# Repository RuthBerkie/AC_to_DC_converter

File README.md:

# AC to DC Converter

This schematic represents a standard linear DC power supply circuit featuring a full-wave bridge rectifier, smoothing filter, and visual power indicator. Its main purpose is to convert alternating current (AC) input into a smooth, stable direct current (DC) output.

1. Component Breakdown & Their Roles

       • J1 (Screw_Terminal_01x02): The AC power input terminal. connecting the external low-voltage AC source, typically coming from a step-down transformer.
       • D1, D3, D4, D5 (1N4007 Diodes): These four diodes form a Full-Wave Bridge Rectifier. Diodes only allow current to flow in one direction. Together, they redirect both the positive and negative halves of the alternating AC wave into a single positive direction, converting AC into pulsating DC.
       • C1 (1000µF Capacitor): The Smoothing/Filter Capacitor. Rectified DC still has massive voltage drops (ripples). C1 stores electrical energy during voltage peaks and releases it during voltage drops, flattening the pulses into a clean, steady DC voltage.
       • R1 (10kΩ Resistor): A Bleeder Resistor. When you turn off or unplug the circuit, C1 can hold a dangerous electrical charge for a long time. R1 provides a safe, continuous path to completely discharge the capacitor when power is disconnected.
       • R2 (2.2kΩ Resistor) & D6 (LED): The Power Indicator. The LED lights up to show that the board is powered and functioning. Because an LED cannot handle raw supply voltage directly, R2 acts as a current-limiting resistor to prevent the LED from burning out.
       • J2 (Screw_Terminal_01x02): The DC power output terminal. This delivers the final, rectified, and smoothed DC voltage to whatever device or external circuit you want to power.
       • H1–H4 (MountingHoles): These are physical holes on the circuit board for screws. They have no electrical function but are used to securely mount the physical PCB into an enclosure.
       • PWR_FLAG & GND: Technical labels used in schematic software (like KiCad). GND establishes the 0V reference line (Ground), while PWR_FLAG informs the software's error-checker that power is properly defined on this net.

The layout follows a logical, left-to-right progression of power processing:
[AC Input: J1] ➔ [Rectification: D1-D5] ➔ [Filtering: C1] ➔ [Bleeding/Indicating: R1, R2+D6] ➔ [DC Output: J2]

    • The AC to Bridge Connections: The two input wires from J1 connect directly to the midpoints of the diode pairs (between D1/D4 and D3/D5). This ensures that regardless of which AC wire is positive at any microsecond, the current is always steered correctly.
    
• Creating the DC Rails:

	• The cathodes (the side with the line symbol) of D1 and D3 join together at the top. This becomes the Positive (+) DC Rail.
	• The anodes of D4 and D5 join together at the bottom. This becomes the Negative (-) DC Rail / Ground.
  
• The Parallel Layout: Components C1, R1, and the R2+D6 branch are connected in parallel across the positive and negative rails.

	• Connecting C1 in parallel allows it to act as a voltage reservoir directly stabilizing the main power lines.
	• Connecting R1 and the LED indicator branch in parallel ensures they continuously experience the full system voltage without blocking current from reaching the final output terminal, J2.

  step-by-step summary of how the entire circuit processes electricity from start to finish:
  
    1. The Input: Alternating Current (AC voltage) enters the circuit through the J1 terminal block on the far left. At this stage, the voltage is constantly fluctuating up and down, reversing its direction multiple times per second.
    2. Rectification: The electricity immediately flows into the Bridge Rectifier (D1, D3, D4, D5). These four diodes act like one-way electrical valves. They redirect the negative halves of the shifting AC wave into the positive direction, transforming it into pulsating Direct Current (DC). 
    3. Smoothing: The pulsating DC moves to the C1 Capacitor. Because the voltage is still pulsing rapidly, the capacitor acts like a temporary water reservoir—it quickly charges up during voltage peaks and discharges energy during the drops. This heavily filters the electrical "ripple," flattening the pulses into a smooth, stable DC voltage.
    4. Safety & Indicator: On its way to the exit, the smooth DC power runs across R1 and R2+D6.
         	• D6 (the LED) lights up to visually confirm the board is active, while R2 keeps the LED from pulling too much current and burning out.
         	• R1 (the bleeder) acts as a safety drain, slowly emptying the stored electrical energy inside the capacitor once the main power source is disconnected.
    5. The Output: The finalized, clean, and reliable DC power exits through the J2 terminal block on the far right, ready to safely run your electronics.

 FINAL RESULT

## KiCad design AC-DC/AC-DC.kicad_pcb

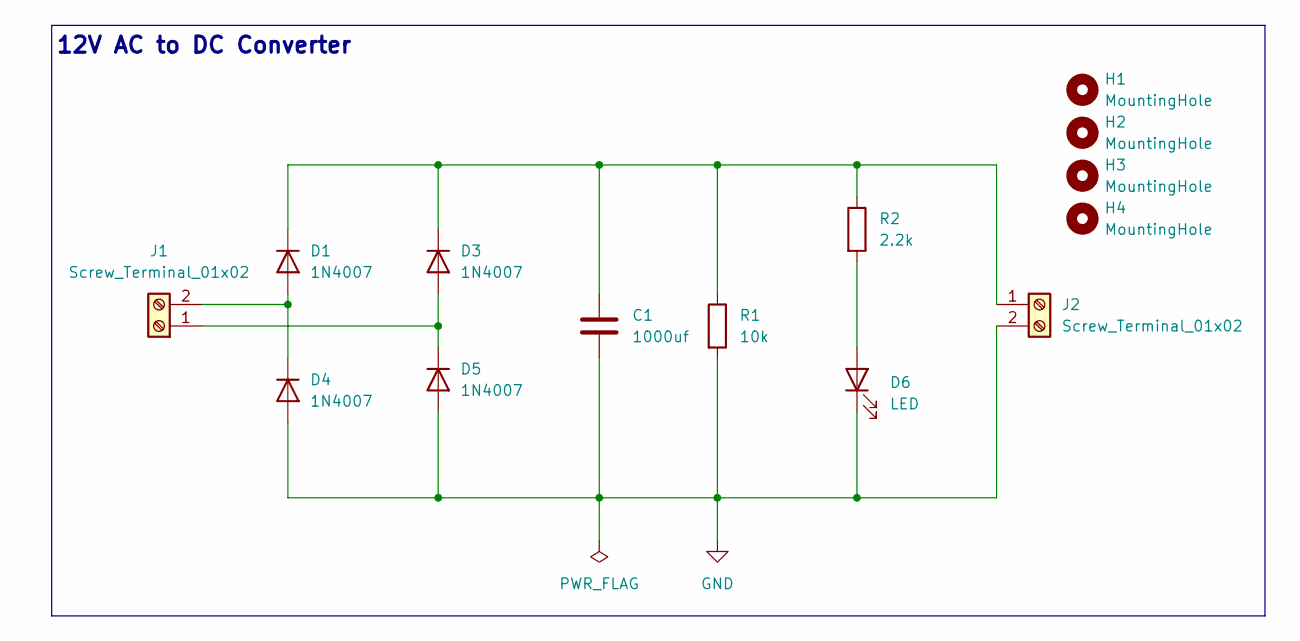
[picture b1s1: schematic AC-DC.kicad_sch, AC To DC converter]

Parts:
C1: 1000uf; CP_Radial_D8.0mm_P3.50mm
D1, D3, D4, D5: 1N4007; D_DO-41_SOD81_P10.16mm_Horizontal
D6: LED; LED_D5.0mm
H1, H2, H3, H4: MountingHole; MountingHole_3.5mm
J1, J2: Screw_Terminal_01x02; TerminalBlock_CUI_TB007-508-02_1x02_P5.08mm_Horizontal
R1: 10k; R_Axial_DIN0207_L6.3mm_D2.5mm_P7.62mm_Horizontal
R2: 2.2k; R_Axial_DIN0207_L6.3mm_D2.5mm_P7.62mm_Horizontal

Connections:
GND: C1.2, D4.2 (A), D5.2 (A), D6.1 (K), J2.2, R1.2
unnamed: D1.2 (A), D4.1 (K), J1.2
unnamed: C1.1, D1.1 (K), D3.1 (K), J2.1, R1.1, R2.1
unnamed: D3.2 (A), D5.1 (K), J1.1
unnamed: D6.2 (A), R2.2

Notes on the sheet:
12V AC to DC Converter

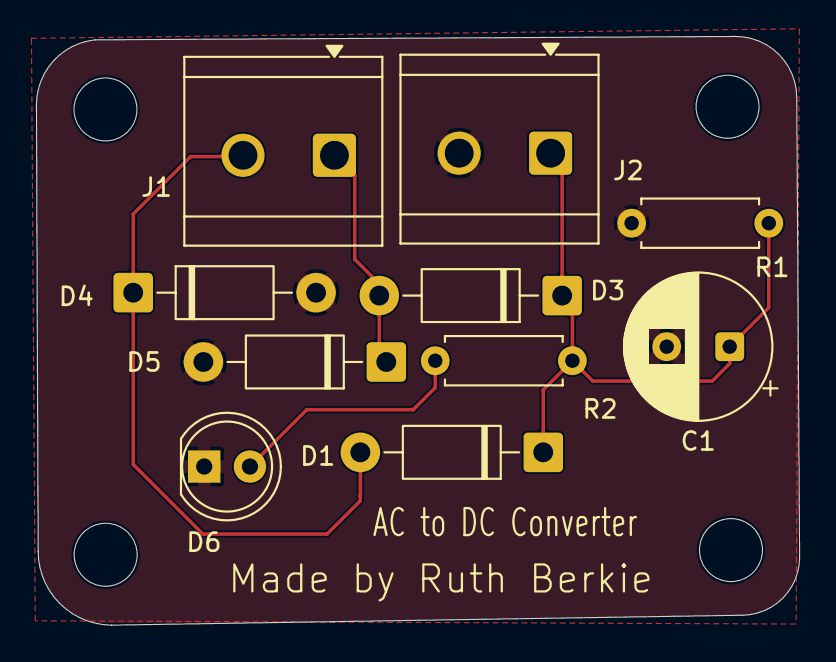
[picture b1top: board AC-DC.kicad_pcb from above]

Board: 2 copper layers, 42.4 x 32.7 mm, 14 parts (0 on the bottom side), 5 nets.
